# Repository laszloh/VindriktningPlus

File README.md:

# VindriktningPlus

 Development here has stopped. Main repo: https://gitlab.com/home-automation9622510/VindriktningPlus

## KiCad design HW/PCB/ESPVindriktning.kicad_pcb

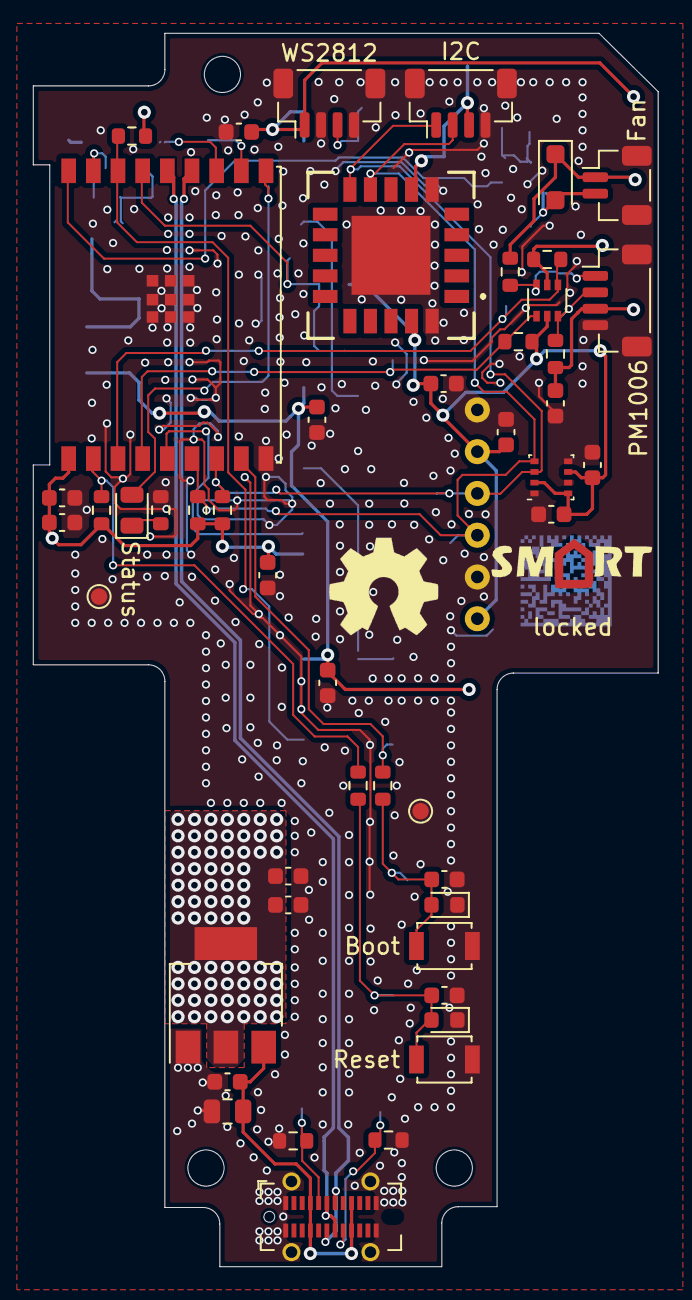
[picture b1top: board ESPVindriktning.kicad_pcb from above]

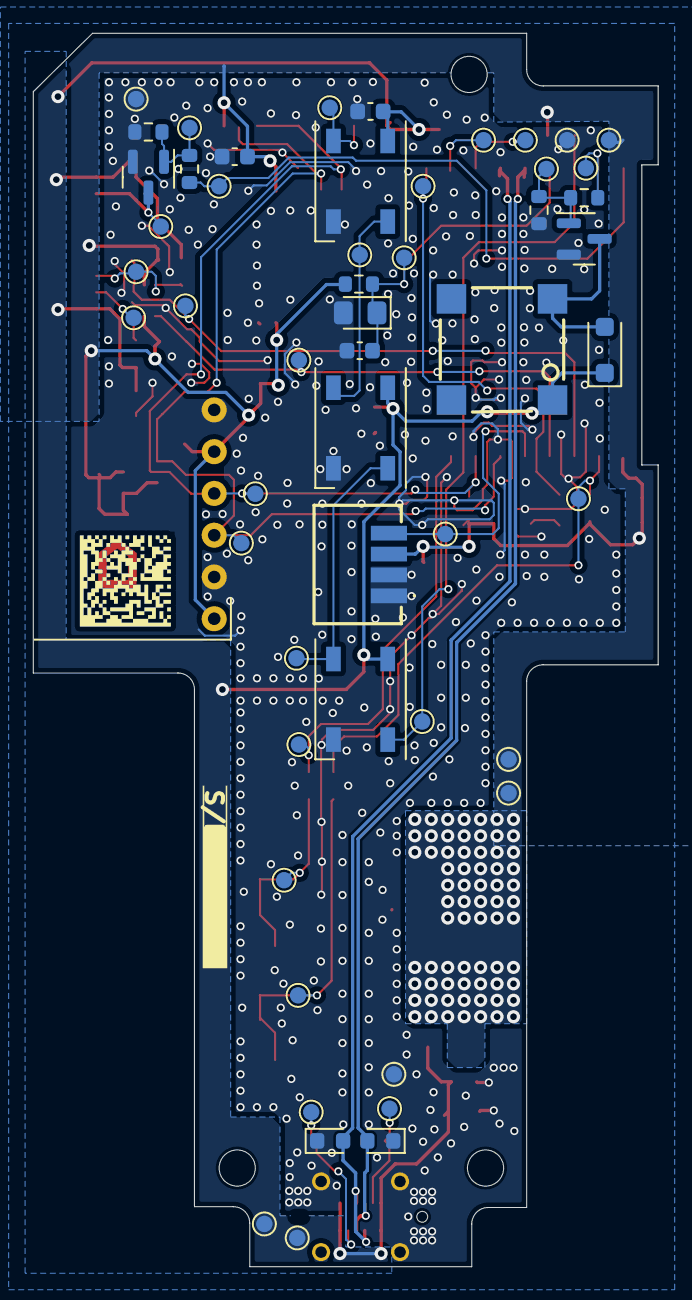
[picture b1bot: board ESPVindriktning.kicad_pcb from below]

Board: 2 copper layers, 38.0 x 75.0 mm, 102 parts (54 on the bottom side), 33 nets.

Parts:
BZ101: Buzzer; CMT752580SMTTR
C101, C118: 1n; C_0603_1608Metric
C102, C103, C104, C106, C107, C109, C110, C111, C113, C114, C115, C116, C117, C119, C120: 100n; C_0603_1608Metric
C105: 22u; C_0805_2012Metric
C108: 22u; C_0603_1608Metric
C112: 2.2u; C_0603_1608Metric
D101, D102, D103, D104: CG0603MLC-05LE; D_0603_1608Metric
D105, D106, D107: WS2812B; LED_WS2812B_PLCC4_5.0x5.0mm_P3.2mm
D108, D109: NRVS1MFL; D_SOD-123F
D110: blue; LED_0805_2012Metric
P101, P102, P103, P104, P105, P106, P107, P108, P109, P110, P111, P112, P113, P114, P115, P116, P117, P118, P119, P120, P121, P122, P123, P124, P125, P126, P127, P128, P129, P130, P131, P132, P134, P135, P136, P137: TestPoint_Small; TestPoint_Pad_D1.0mm
PD101: SFH 3716; LED_0805_2012Metric_Pad1.15x1.40mm_HandSolder
R101, R107, R108, R109, R112, R113, R114, R118: 10k; R_0603_1608Metric
R102, R103: 5.1k; R_0603_1608Metric
R104: 47k; R_0603_1608Metric
R105, R106: 10R; R_0603_1608Metric
R110, R111: 1.2k; R_0603_1608Metric
R115: 470R; R_0603_1608Metric
R116, R117: 100R; R_0603_1608Metric
S101: TLV76133DCYR; SOT-223-3_TabPin2
S102: ESP32-C3-WROOM-02
S103: TSOP36238TT
S104: SCD40; SCD40DR2
S105: BME280; module_bme280
S106: BME280; Bosch_LGA-8_2.5x2.5mm_P0.65mm_ClockwisePinNumbering
SW101: reset; SW_SPST_B3U-1000P
SW102: boot; SW_SPST_B3U-1000P
T101, T102: BSS138; SOT-23
TN101: FDG1024NZ; SOT-363_SC-70-6
X101: USB_C; USB_C_Receptacle_GCT_USB4115-03-C
X102: WS2812; JST_SH_BM04B-SRSS-TB_1x04-1MP_P1.00mm_Vertical
X105: Fan; JST_SH_BM02B-SRSS-TB_1x02-1MP_P1.00mm_Vertical
X106: PM1006; JST_SH_BM04B-SRSS-TB_1x04-1MP_P1.00mm_Vertical
X107: I2C; JST_SH_BM04B-SRSS-TB_1x04-1MP_P1.00mm_Vertical

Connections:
+3.3V: C102.1, C108.2, C109.2, C111.1, C112.1, C113.1, C114.1, C116.1, C119.1, C120.1, P116.1, P135.1, P136.1, R101.2, R104.2, R107.2, R110.2, R111.2, R113.2, R118.2, S101.2 (VO), S102.1 (3V3), S103.3 (Vs), S104.7 (VDD), S104.19 (VDDH), S105.1 (VCC), S105.5 (CSB), S106.2 (CSB), S106.6 (VDDIO), S106.8 (VDD), TN101.2 (G), TN101.5 (G), X107.3
+5V: BZ101.1 (-), C103.1, C104.1, C105.2, C106.2, C107.1, C110.1, C117.1, D105.1 (VDD), D106.1 (VDD), D107.1 (VDD), D108.1 (K), D109.1 (K), P110.1, P134.1, R112.2, R114.2, S101.3 (VI), X101.A4 (VBUS), X101.A9 (VBUS), X101.B4 (VBUS), X101.B9 (VBUS), X102.1, X105.1, X106.3
/BOOT: P126.1, R116.1, S102.8 (GPIO9)
/BOOT_BTN: C118.1, D102.2 (A2), P102.1, R116.2, SW102.2
/BRIGHT_VAL: C115.1, P121.1, PD101.1 (C), R104.1, S102.15 (GPIO3/ADC1_CH3)
/BUZZER: P109.1, R106.1, S102.17 (GPIO1/ADC1_CH1/XTAL_32K_N)
/BUZ_D: BZ101.2 (+), D108.2 (A), T101.3 (D)
/BUZ_G: P132.1, R106.2, R108.2, T101.1 (G)
/CC1: P104.1, R103.2, X101.A5 (CC1)
/CC2: P105.1, R102.2, X101.B5 (CC2)
/FAN: P108.1, R105.1, S102.18 (GPIO0/ADC1_CH0/XTAL_32K_P)
/FAN_D: D109.2 (A), P130.1, T102.3 (D), X105.2
/FAN_G: P129.1, R105.2, R109.2, T102.1 (G)
/I2C_SCL: P124.1, R111.1, S102.6 (GPIO7), S104.9 (SCL), S105.3 (SCL), S106.4 (SCK), X107.2
/I2C_SDA: P125.1, R110.1, S102.7 (GPIO8), S104.10 (SDA), S105.4 (SDA), S106.3 (SDI), X107.1
/IR_OUT: P123.1, S102.5 (GPIO6), S103.4 (OUT)
/PM_RX: P122.1, R107.1, S102.4 (GPIO5/ADC2_CH0), TN101.1 (S)
/PM_TX: P117.1, R113.1, S102.3 (GPIO4/ADC1_CH4), TN101.4 (S)
/RX: P131.1, R114.1, TN101.3 (D), X106.2
/RXD0: P119.1, S102.12 (GPIO21/U0TXD)
/STATUS_LED: D110.2 (A), P127.1, S102.10 (GPIO10)
/STATUS_LED_R: D110.1 (K), R115.2
/TX: P128.1, R112.1, TN101.6 (D), X106.1
/TXD0: P118.1, S102.11 (GPIO20/U0RXD)
/USB_D+: D103.2 (A2), S102.14 (GPIO19/USB_D+), X101.A6 (D+), X101.B6 (D+)
/USB_D-: D104.2 (A2), S102.13 (GPIO18/USB_D-), X101.A7 (D-), X101.B7 (D-)
/WS2812_1_DO: D105.2 (DOUT), D106.4 (DIN), P103.1
/WS2812_2_DO: D106.2 (DOUT), D107.4 (DIN), P107.1
/WS2812_3_DO: D107.2 (DOUT), P112.1, X102.3
/WS2812_DI: D105.4 (DIN), P120.1, R118.1, S102.16 (GPIO2/ADC1_CH2)
/~RESET: P106.1, R101.1, R117.1, S102.2 (EN/CHIP_PU)
/~RST_BTN: C101.1, D101.2 (A2), P101.1, R117.2, SW101.2
GND: C101.2, C102.2, C103.2, C104.2, C105.1, C106.1, C107.2, C108.1, C109.1, C110.2, C111.2, C112.2, C113.2, C114.2, C115.2, C116.2, C117.2, C118.2, C119.2, C120.2, D101.1 (A1), D102.1 (A1), D103.1 (A1), D104.1 (A1), D105.3 (VSS), D106.3 (VSS), D107.3 (VSS), P111.1, P113.1, P114.1, P115.1, P137.1, PD101.2 (E), R102.1, R103.1, R108.1, R109.1, R115.1, S101.1 (GND), S102.9 (GND), S102.19 (GND), S103.1 (GND), S103.2 (GND), S104.6 (GND), S104.20 (GND), S104.21 (GND), S105.2 (GND), S105.6 (SDO), S106.1 (GND), S106.5 (SDO), S106.7 (GND), SW101.1, SW102.1, T101.2 (S), T102.2 (S), X101.A1 (GND), X101.A12 (GND), X101.B1 (GND), X101.B12 (GND), X101.S1 (SHIELD), X102.2, X102.4, X102.MP (MountPin), X105.MP (MountPin), X106.4, X106.MP (MountPin), X107.4, X107.MP (MountPin)

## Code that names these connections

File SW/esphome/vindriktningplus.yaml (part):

substitutions:
  # pinout
  FAN_PIN: GPIO0
  BUZZER_PIN: GPIO1
  WS2812_PIN: GPIO2
  BRIGHT_PIN: GPIO3
  PM_TX_PIN: GPIO4
  PM_RX_PIN: GPIO5
  IR_REC_PIN: GPIO6
  I2C_SCL: GPIO7
  I2C_SDA: GPIO8
  # BOOT_PIN: GPIO9
  INT_LED_PIN: GPIO10
  # default values
  SCD4x_update_interval: 60s
  temp_calibration: "-4"
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
# uart used for PM1006 exclusively
uart:
  rx_pin: $PM_TX_PIN
  tx_pin: $PM_RX_PIN
  baud_rate: 9600
  id: uart_a

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
output:
  - platform: ledc
    pin: $FAN_PIN
    frequency: 25kHz
    id: pm1006_fan
    channel: 0
  - platform: ledc
    pin: $BUZZER_PIN
    channel: 2
    id: buzzer_out

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      from: 2
      to: 2
  - platform: esp32_rmt_led_strip
    pin: GPIO2
    rgb_order: GRB
    num_leds: 3
    rmt_channel: 0
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
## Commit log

2024-01-30 Schematic ready for review
2024-01-30 Implement review findings
2024-01-31 Add first layout tryout
2024-02-03 Review and layout optimization
    Changes to schematic:
    - Add BME280 as ASIC under the module
    - Reduce I2C Pull-Ups to 1.2k
    Changes to layout:
    - Optimize parts placement
    - Make USB approx. 9ß OHm impedance
2024-02-03 ESP32-C3 pinout change
    Change pinout due to GPIO2 needing a Pull-Up (strapping pin)
2024-02-03 Add first version of esphome
    Add ESPHome files for the VindriktningPlus.
    Supported active modules:
    - PM1006 + extractor fan
    - SCD40
    - BM280
    - 3x WS2812
2024-02-05 Add standalone mode, if HA API is not connected
2024-02-09 Add testpoints to schematic and layout
    Implement improvements from Andreas (Breaker04)
2024-02-10 Add GND stitching, PCB production information and clean up silkscreen and fab layers
2024-02-10 Rename folder to PCB
2024-02-10 Move ESP32 further into the PCB and replace IR receiver with smaller package
2024-02-11 Layout modifications to fit into housing
2024-02-11 Add reverse engineered housing to test PCB fit
2024-02-11 Added final touches to the layout
2024-02-12 Add DMC code and S/N Fields
2024-02-12 Add substitutions for hard coded values
    Use substitutions for the pinout, hard coded update intervals and limits for qir quality.
2024-02-12 A lot of changes
2024-02-15 Clean up schematic and layout further
2024-02-16 Fix DRC violations
2024-02-16 Add panelization configuration and prepare for sample production
2024-02-19 Change Copper Pour distance to 0.3mm
    Rework GND plane stitching and copper fillings.
2024-02-19 Even more PCB layout cleanup
2024-02-20 Cleanup of the Silkscreen layer and minor changes in routing
